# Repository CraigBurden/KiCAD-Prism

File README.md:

# KiCAD Prism

KiCAD Prism is an open-source, self-hosted review, release and
component-governance platform for teams that design in KiCad and keep their
projects in Git.

KiCad remains the editor and Git remains the source of truth. Prism adds what
happens around them: browsing every revision in the browser, reviewing changes
with comments, building and signing off release packages, and running a governed
component library that desktop KiCad places parts from. It runs on your own
hardware, with no proprietary ECAD cloud.

*The designs in these screenshots are third-party hardware projects, used to
show Prism working on real boards. They are not made by Prism. See
[Designs shown in the screenshots](#designs-shown-in-the-screenshots).*

## What Prism does

### Browse and review any revision

Import projects from SSH or HTTPS Git remotes, monorepos included. Every
revision opens in schematic, PCB, 3D, BOM and stackup views, with cross-probing
between them, net highlighting, point-to-point measurement and PCB or schematic
insets. Prism reads each revision once with its own Rust KiCad parser and keeps
the result as a design bundle, so recent commits and every tag open without
waiting.

| Schematic | PCB | 3D |
| --- | --- | --- |
|  |  |  |

Insets open a live view of the other document from any pin or pad, and chain
from there: below, a PCB inset of U1's CC1 pin leads to a schematic inset of C7.

Select a net to highlight it across the schematic, PCB and 3D views, with its
routed length, layers, tracks and vias. In 3D, isolate a net to see only its
copper: tracks, zones, pads and vias.

| Net highlight (PCB) | Net highlight (3D) | Net isolated (3D) |
| --- | --- | --- |
|  |  |  |

Comment on any sheet, part or area. Comments are rich text with pasted snips
and attachments, anchored to the revision they were written on, and can be
published to GitHub or GitLab issues.

### Compare revisions

Compare any two revisions. Design Comparison lists what changed in the
schematic, PCB, BOM, stackup and fabrication outputs, highlights it on the
sheet, and keeps the review discussion next to it.

### Release a board

Release Studio takes a committed revision through source, identity,
manufacturing, build, outputs and publish. It builds fabrication and assembly
files, PDF documents and manufacturer packs, shows the Gerbers in the browser,
records DRC/ERC evidence and designer and QA sign-off, and publishes the
approved package to GitHub or GitLab Releases.

### Govern components

Library Manager is a component catalog with immutable revisions, reusable
symbol, footprint, 3D and SPICE assets, optional KiCad Library Convention
checks and a QA release flow. Components can be imported from library folders
or from the parts your projects already use. Released parts reach desktop KiCad
through the Remote Symbol Provider, which places the exact catalog revision with
its 3D models embedded, or through a generated KiCad database library.

In KiCad, the Remote Symbol Provider panel shows a released part's details and
symbol and footprint previews, and places it.

### Document a design

Generated documents are built from the same design bundle. The connector
interface control sheet below, one per connector with views from its STEP model,
a board locator and the pinout with the nets each pin reaches, comes from the
documentation prototypes in [`native/src/rs/prism-docs-lab`](native/src/rs/prism-docs-lab/README.md).
The prototypes are run by hand and are not part of the product yet.

### Also included

- Assets Portal and Workflows for KiCad jobset outputs, and a Documentation
  view for the Markdown kept in a project.
- Design variants with effective BOM and DNP visibility.
- Simulation Studio (experimental, off by default): DC IR drop on a revision's
  board.
- OIDC single sign-on, optional password login, workspace roles, OAuth2 for the
  KiCad panel and scoped service clients for automation.

## Designs shown in the screenshots

The screenshots show publicly available KiCad projects by other designers,
imported into Prism the way a team would import its own. Their schematics,
layouts, 3D models, documentation and design decisions are the work of their
authors. They were not designed, generated or modified by Prism or its
contributors, and they appear here only to show what Prism does with a real
design. All rights stay with the authors under the projects' own terms.

| Project | Author | Source | License |
| --- | --- | --- | --- |
| Cynthion | Great Scott Gadgets | [greatscottgadgets/cynthion-hardware](https://github.com/greatscottgadgets/cynthion-hardware) | CERN-OHL-P v2 |
| WREN (vme-wren, vme-wren-fp-single, EDA-04903, EDA-04949) | CERN, BE-CEM | [be-cem-edl/chronos/wren/wren-hw](https://gitlab.cern.ch/be-cem-edl/chronos/wren/wren-hw) | CERN-OHL-W v2 or later and CC BY-SA 4.0, as stated on the schematic sheets |
| OpenSwitch 10x10G carrier and LAN969x | Quentin Freimanis | [qfreiman/openswitch-10x10g-carrier](https://gitlab.com/qfreiman/openswitch-10x10g-carrier), [qfreiman/openswitch-lan969x](https://gitlab.com/qfreiman/openswitch-lan969x) | No license is stated in the repositories; see them for the author's terms |
| USB-PD-Trigger-Board | Krishna Swaroop (Prism maintainer) | [krishna-swaroop/USB-PD-Trigger-Board](https://github.com/krishna-swaroop/USB-PD-Trigger-Board) | MIT |

The component catalog in the Library Manager screenshot is CERN's public
KiCad database library. If you are an author of one of these designs and would
like a screenshot changed, credited differently or removed, please
[open an issue](https://github.com/krishna-swaroop/KiCAD-Prism/issues).

## Runtime

| Service | Purpose |
| --- | --- |
| `frontend` | React application and Nginx reverse proxy |
| `backend` | FastAPI, authentication, authorization, and APIs |
| `prism-worker` | project, comparison, visualization, and jobset work |
| `catalog-worker` | catalog import, validation, preview, and release work |
| `postgres` | workspace, comments, catalog, jobs, audit, and session data |

The API and both workers reuse one Prism backend image. Imported repositories
and generated assets live under `data/projects`; Git SSH state lives under
`data/ssh`. PostgreSQL and both directories are required for complete recovery.

See [Architecture](https://krishna-swaroop.github.io/KiCAD-Prism/contribute/architecture/).

## Deploy the latest stable release

Normal users should open the
[latest stable GitHub Release](https://github.com/krishna-swaroop/KiCAD-Prism/releases/latest)
and download its Linux AMD64 deployment archive and checksum.

Each generated bundle contains a pull-only Compose file and exact Prism image
digests:

```bash
sha256sum -c kicad-prism-vX.Y.Z-linux-amd64.tar.gz.sha256
tar -xzf kicad-prism-vX.Y.Z-linux-amd64.tar.gz
cd kicad-prism-vX.Y.Z-linux-amd64
sha256sum -c SHA256SUMS
cp .env.example .env
# Configure authentication, domain, database password, and session secret.
docker compose pull
docker compose up -d --wait
```

The supported public deployment target is Linux AMD64. Native ARM64 release
images are not currently published.

Follow [Deployment](https://krishna-swaroop.github.io/KiCAD-Prism/admin/deployment/) for OIDC, TLS, storage, sizing, and
production checks. If a historical release predates deployment bundles, build
that stable tag from source as documented there.

## First-time setup with the guided installer

For a first deployment from a source checkout, the guided installer can render
the environment and proxy configuration for you instead of requiring every
Compose setting to be assembled by hand. It supports Linux, macOS, WSL2, and
Windows PowerShell, and requires Python 3.9 or newer plus Docker Compose v2.

From the repository root, run the launcher for your platform:

```bash
./deploy.sh
```

```powershell
.\deploy.ps1
```

The installer asks which HTTPS/network scheme applies, collects the required
OIDC and deployment settings, runs preflight and network checks, and writes the
generated configuration under `generated/`. The output includes the environment
file, proxy configuration, Compose overlay, a redacted run record, and a
`NEXT_STEPS.md` checklist. Review the generated files before starting the
services, or let the installer start them after all checks pass:

```bash
./deploy.sh --start
```

Useful first-run modes include:

```bash
./deploy.sh --dry-run                         # render without writing files
./deploy.sh --fresh                           # ignore existing generated config
./deploy.sh --answers answers.json --non-interactive
```

Generated configuration contains deployment secrets and is excluded from Git;
back it up with the rest of the Prism deployment state. The installer is a
guided configuration layer, not a replacement for the [Deployment](https://krishna-swaroop.github.io/KiCAD-Prism/admin/deployment/)
and [Operations](https://krishna-swaroop.github.io/KiCAD-Prism/admin/operations/) guides. For a stable release archive,
follow the pull-only bundle instructions above and use the installer only when
working from a source checkout that includes `deploy.sh` or `deploy.ps1`.

## Develop from source

All feature development and source testing happen through `dev`:

```bash
git clone --branch dev https://github.com/krishna-swaroop/KiCAD-Prism.git
cd KiCAD-Prism
cp .env.example .env
docker compose up --build -d
```

For a private local evaluation, explicitly set `AUTH_ENABLED=false`. Never use
guest administrator mode on a shared or reachable host.

See [Getting started](https://krishna-swaroop.github.io/KiCAD-Prism/get-started/try-it/) and
[Contributing](CONTRIBUTING.md).

## Branch and release model

- Feature, fix, documentation, and refactor branches merge into protected
  `dev` through pull requests.
- `dev` is the integration branch for the next release.
- Tested release scope is merged from `dev` into protected `main`.
- A semantic-version tag on a quality-gated `main` commit builds, smoke-tests,
  and publishes the AMD64 images and deployment bundle.
- Pull requests and ordinary branch pushes never publish container images.

See [Release process](https://krishna-swaroop.github.io/KiCAD-Prism/contribute/release-process/).

## Documentation

- [Documentation index](docs/README.md)
- [Platform overview](https://krishna-swaroop.github.io/KiCAD-Prism/get-started/what-is-prism/)
- [Getting started](https://krishna-swaroop.github.io/KiCAD-Prism/get-started/try-it/)
- [Deployment](https://krishna-swaroop.github.io/KiCAD-Prism/admin/deployment/)
- [Configuration](docs/CONFIGURATION.md)
- [Authentication and access](https://krishna-swaroop.github.io/KiCAD-Prism/admin/authentication/)
- [Project workflows](https://krishna-swaroop.github.io/KiCAD-Prism/use/projects/)
- [Library Manager](https://krishna-swaroop.github.io/KiCAD-Prism/use/library-manager/)
- [Remote Symbol Provider](docs/REMOTE_SYMBOL_PROVIDER.md)
- [Release Studio](docs/release-studio/README.md)
- [Issue trackers](https://krishna-swaroop.github.io/KiCAD-Prism/admin/issue-trackers/)
- [Simulation Studio](https://krishna-swaroop.github.io/KiCAD-Prism/use/simulation-studio/)
- [Team adoption](https://krishna-swaroop.github.io/KiCAD-Prism/get-started/team-adoption/)
- [Operations](https://krishna-swaroop.github.io/KiCAD-Prism/admin/operations/)
- [Upgrades and backups](https://krishna-swaroop.github.io/KiCAD-Prism/admin/upgrades/)
- [Release process](https://krishna-swaroop.github.io/KiCAD-Prism/contribute/release-process/)

## Project status

`main` contains stable release history; the latest release is
[`v5.0.2-alpha`](https://github.com/krishna-swaroop/KiCAD-Prism/releases/tag/v5.0.2-alpha).
`dev` holds unreleased work and may change between releases.

Current boundaries include:

- a single-workspace deployment, not multi-tenant SaaS;
- one role per user rather than composable workspace and catalog permissions;
- mentions are stored but send no email or inbox notifications;
- issue publication covers GitHub and GitLab; Gitea and Forgejo issues, pull
  request status checks and built-in PLM connectors are not shipped;
- fixed workflow types rather than first-class arbitrary workflows;
- no real-time multi-user ECAD editing.

See [Platform overview](https://krishna-swaroop.github.io/KiCAD-Prism/get-started/what-is-prism/) before planning a team rollout.

## Contributing and issues

- [Contributing guidelines](CONTRIBUTING.md)
- [Reporting issues](https://krishna-swaroop.github.io/KiCAD-Prism/contribute/reporting-issues/)
- [Security policy](SECURITY.md)

Changes target protected `dev` through pull requests. The required quality gate
validates frontend, backend, semantic viewer, the native Rust workspace and its
projection parity, source Compose, and release deployment configuration.

## Acknowledgements

Prism builds on work from the KiCad ecosystem, including:

- [ecad-viewer](https://github.com/Huaqiu-Electronics/ecad-viewer)
- [KiCanvas](https://github.com/theacodes/kicanvas)
- [kicad-monkey](https://github.com/wavenumber-eng/kicad_monkey)
- [Interactive HTML BOM](https://github.com/openscopeproject/InteractiveHtmlBom)

## License

KiCAD Prism is licensed under the [Apache License 2.0](LICENSE).

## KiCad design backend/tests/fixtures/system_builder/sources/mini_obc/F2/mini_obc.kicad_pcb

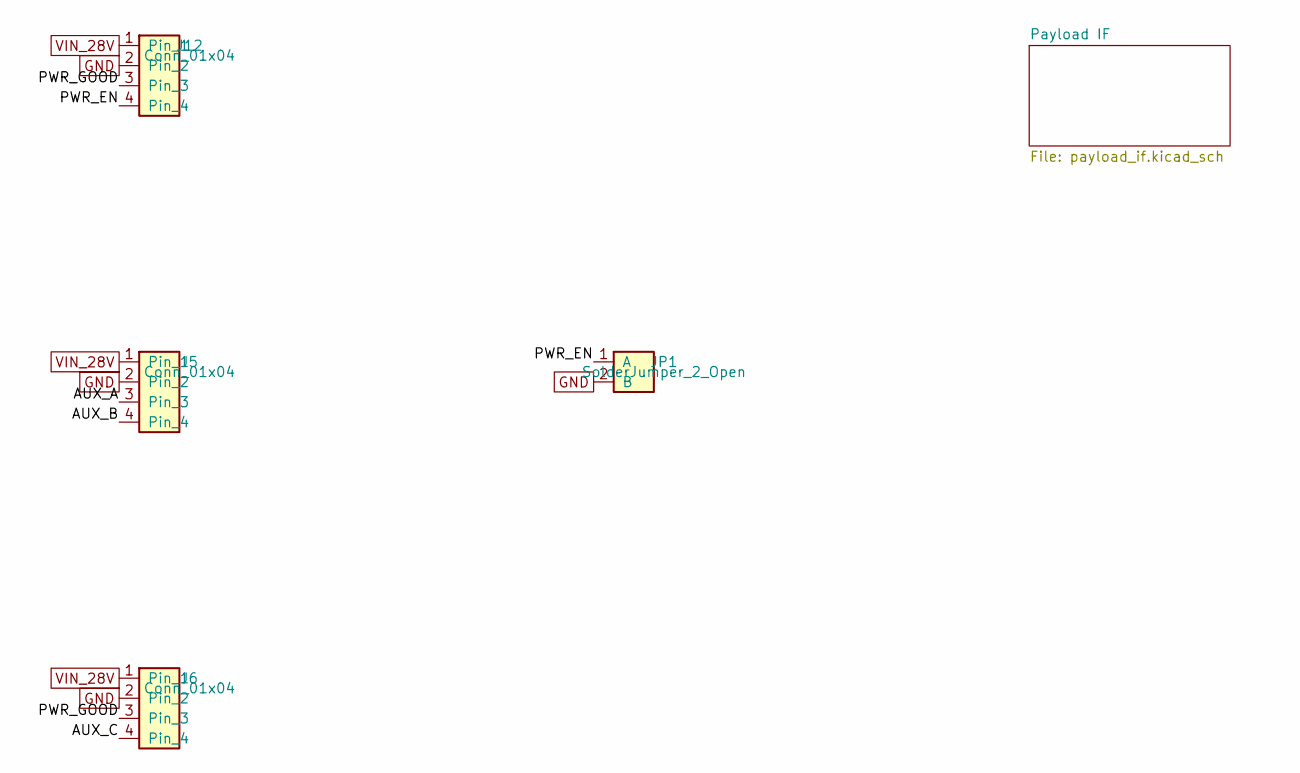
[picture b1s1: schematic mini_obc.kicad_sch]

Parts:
J5, J6, J12: Conn_01x04; PinHeader_1x04_P2.54mm_Vertical
JP1: SolderJumper_2_Open; SolderJumper-2_P1.3mm_Open_Pad1.0x1.5mm

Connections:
/AUX_A: J5.3
/AUX_B: J5.4
/AUX_C: J6.4
/PWR_EN: J12.4, JP1.1 (A)
/PWR_GOOD: J6.3, J12.3
GND: J5.2, J6.2, J12.2, JP1.2 (B); also elsewhere on the board
VIN_28V: J5.1, J6.1, J12.1

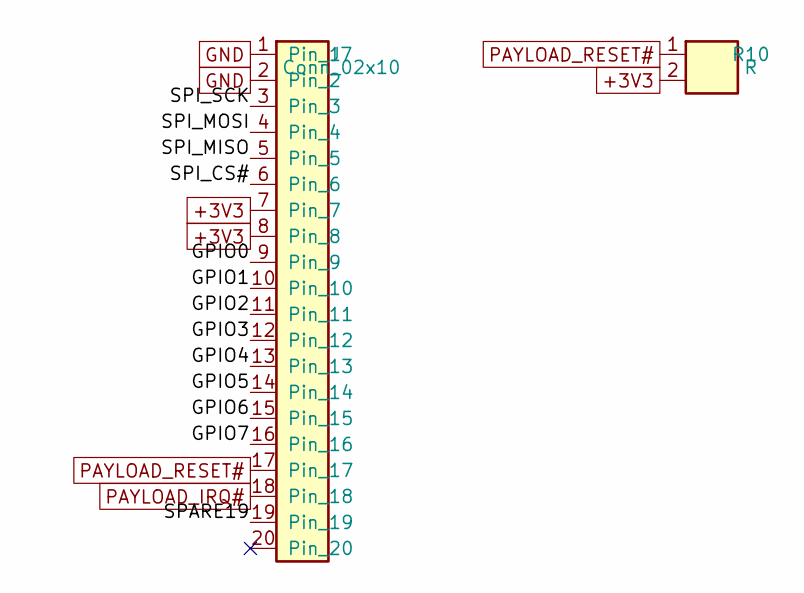
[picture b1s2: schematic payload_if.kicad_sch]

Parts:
J7: Conn_02x10; PinHeader_2x10_P2.54mm_Vertical
R10: R; R_0603_1608Metric

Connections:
+3V3: J7.7, J7.8, R10.2
/Payload IF/GPIO0: J7.9
/Payload IF/GPIO1: J7.10
/Payload IF/GPIO2: J7.11
/Payload IF/GPIO3: J7.12
/Payload IF/GPIO4: J7.13
/Payload IF/GPIO5: J7.14
/Payload IF/GPIO6: J7.15
/Payload IF/GPIO7: J7.16
/Payload IF/SPARE19: J7.19
/Payload IF/SPI_CS#: J7.6
/Payload IF/SPI_MISO: J7.5
/Payload IF/SPI_MOSI: J7.4
/Payload IF/SPI_SCK: J7.3
GND: J7.1, J7.2; also elsewhere on the board
PAYLOAD_IRQ#: J7.18
PAYLOAD_RESET#: J7.17, R10.1

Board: 2 copper layers, 6 parts (0 on the bottom side), 6 nets, no tracks yet.

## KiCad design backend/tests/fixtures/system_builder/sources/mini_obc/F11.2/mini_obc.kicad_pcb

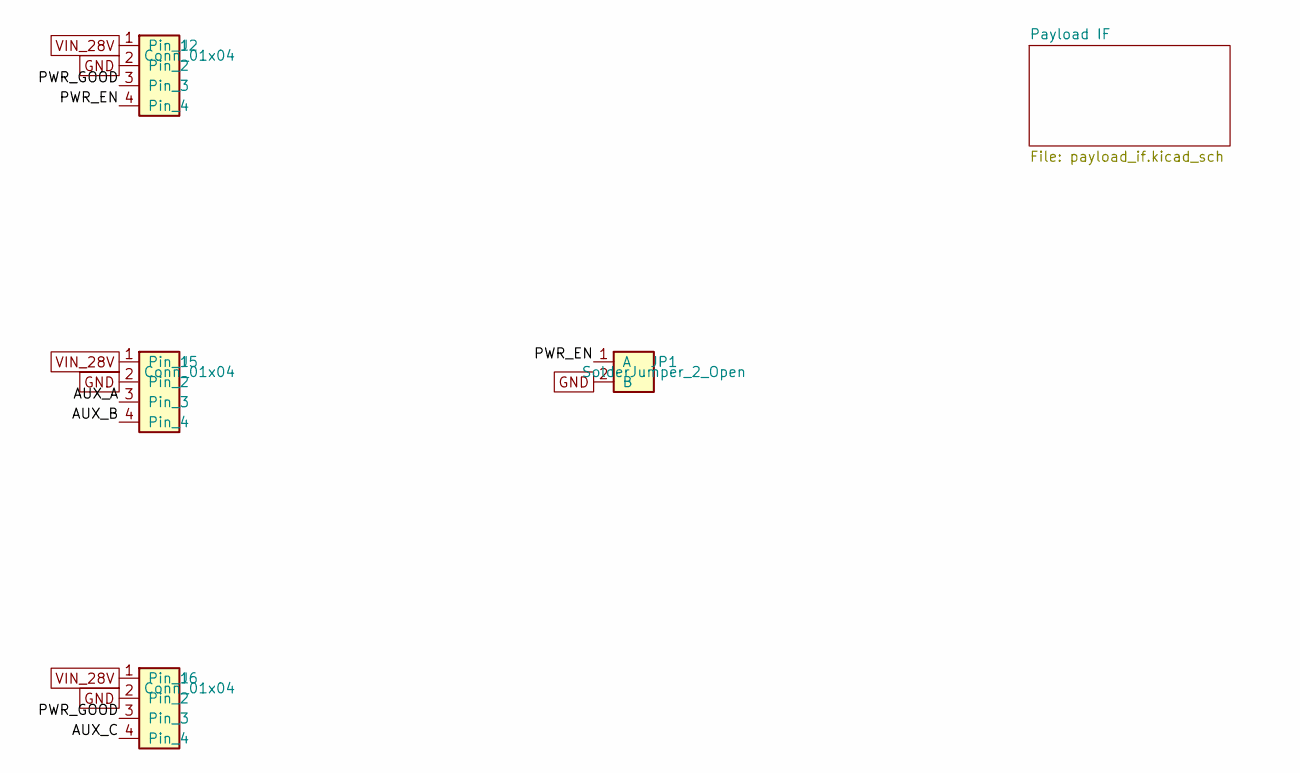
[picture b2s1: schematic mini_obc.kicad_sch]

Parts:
J2, J5, J6: Conn_01x04; PinHeader_1x04_P2.54mm_Vertical
JP1: SolderJumper_2_Open; SolderJumper-2_P1.3mm_Open_Pad1.0x1.5mm

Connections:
/AUX_A: J5.3
/AUX_B: J5.4
/AUX_C: J6.4
/PWR_EN: J2.4, JP1.1 (A)
/PWR_GOOD: J2.3, J6.3
GND: J2.2, J5.2, J6.2, JP1.2 (B); also elsewhere on the board
VIN_28V: J2.1, J5.1, J6.1

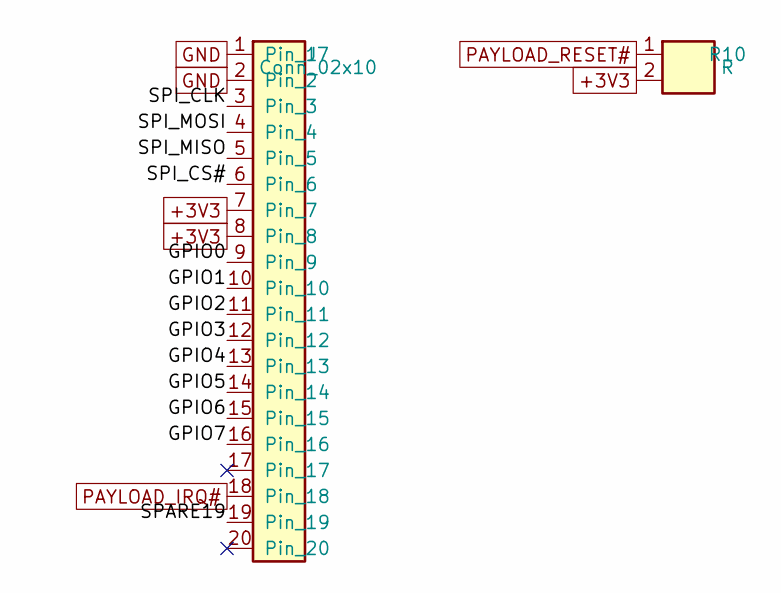
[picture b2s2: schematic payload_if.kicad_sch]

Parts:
J7: Conn_02x10; PinHeader_2x10_P2.54mm_Vertical
R10: R; R_0603_1608Metric

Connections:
+3V3: J7.7, J7.8, R10.2
/Payload IF/GPIO0: J7.9
/Payload IF/GPIO1: J7.10
/Payload IF/GPIO2: J7.11
/Payload IF/GPIO3: J7.12
/Payload IF/GPIO4: J7.13
/Payload IF/GPIO5: J7.14
/Payload IF/GPIO6: J7.15
/Payload IF/GPIO7: J7.16
/Payload IF/SPARE19: J7.19
/Payload IF/SPI_CLK: J7.3
/Payload IF/SPI_CS#: J7.6
/Payload IF/SPI_MISO: J7.5
/Payload IF/SPI_MOSI: J7.4
GND: J7.1, J7.2; also elsewhere on the board
PAYLOAD_IRQ#: J7.18
PAYLOAD_RESET#: R10.1

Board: 2 copper layers, 6 parts (0 on the bottom side), 5 nets, no tracks yet.

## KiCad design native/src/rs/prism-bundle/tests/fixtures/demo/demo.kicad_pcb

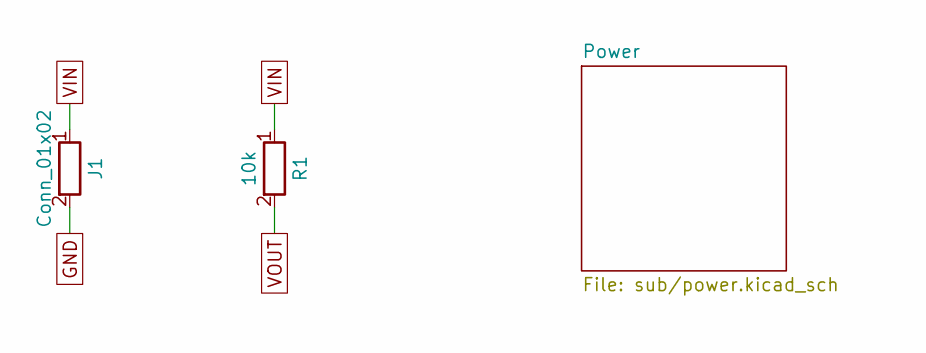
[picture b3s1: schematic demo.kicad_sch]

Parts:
J1: Conn_01x02; PinHeader_1x02_P2.54mm_Vertical
R1: 10k; R_0603_1608Metric

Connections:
GND: J1.2; also elsewhere on the board
VIN: J1.1, R1.1
VOUT: R1.2; also elsewhere on the board

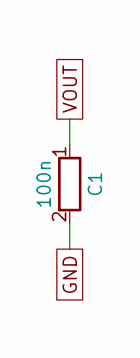
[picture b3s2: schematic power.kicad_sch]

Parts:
C1: 100n; C_0603_1608Metric

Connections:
GND: C1.2; also elsewhere on the board
VOUT: C1.1; also elsewhere on the board

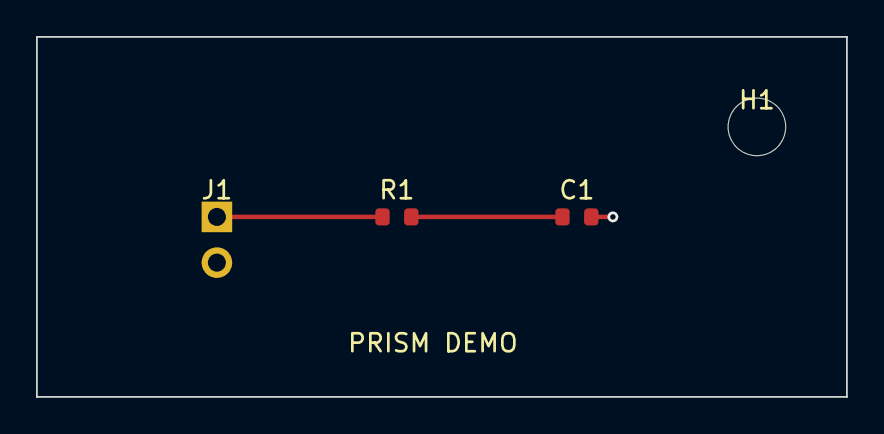
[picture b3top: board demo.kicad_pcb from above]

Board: 2 copper layers, 45.0 x 20.0 mm, 4 parts (0 on the bottom side), 3 nets.

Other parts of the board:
H1: MountingHole; MountingHole_3.2mm_M3
